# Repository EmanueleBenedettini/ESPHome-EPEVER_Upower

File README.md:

# ESPHome-EPEVER_Upower

Code and instructions for the integration of EPEVER Upower inverters in Home Assistant.

## Configuration

In `upower.yaml`, update the following values to match your setup:

- **Line 19**: `YOURAPIENCRYPTIONKEY` - Your API encryption key
- **Line 22**: `YOUROTAPASSWORD` - Your OTA password
- **Line 31**: `YOURPASSWORD` - Your device password

## Firmware Size

The code is optimized to fit on an ESP01_1M module while maintaining OTA update capability.

## Board Design

A custom PCB design is included (created with Eagle). To manufacture your board:

1. Go to a site like [jlcpcb.com](https://jlcpcb.com)
2. Upload the `Gerber.zip` file

### Components to Solder

| Designator | Value | Package |
|---|---|---|
| R5, R6 | 3.3kΩ | M1206 |
| R1, R2 | 10kΩ | M1206 |
| R4 | 120Ω | M1206 |
| U2 | AMS1117-3.3 | SOT229P700X180-4N |
| Q1 | 2N7002 N-Channel MOSFET | SOT23 |
| IC1 | MAX485 | SO08 |
| C1, C2 | 100µF | 6mm diameter |

### Notes

- **U1** (ESP01): In most cases, this does not need to be soldered. It should fit snugly in the socket.

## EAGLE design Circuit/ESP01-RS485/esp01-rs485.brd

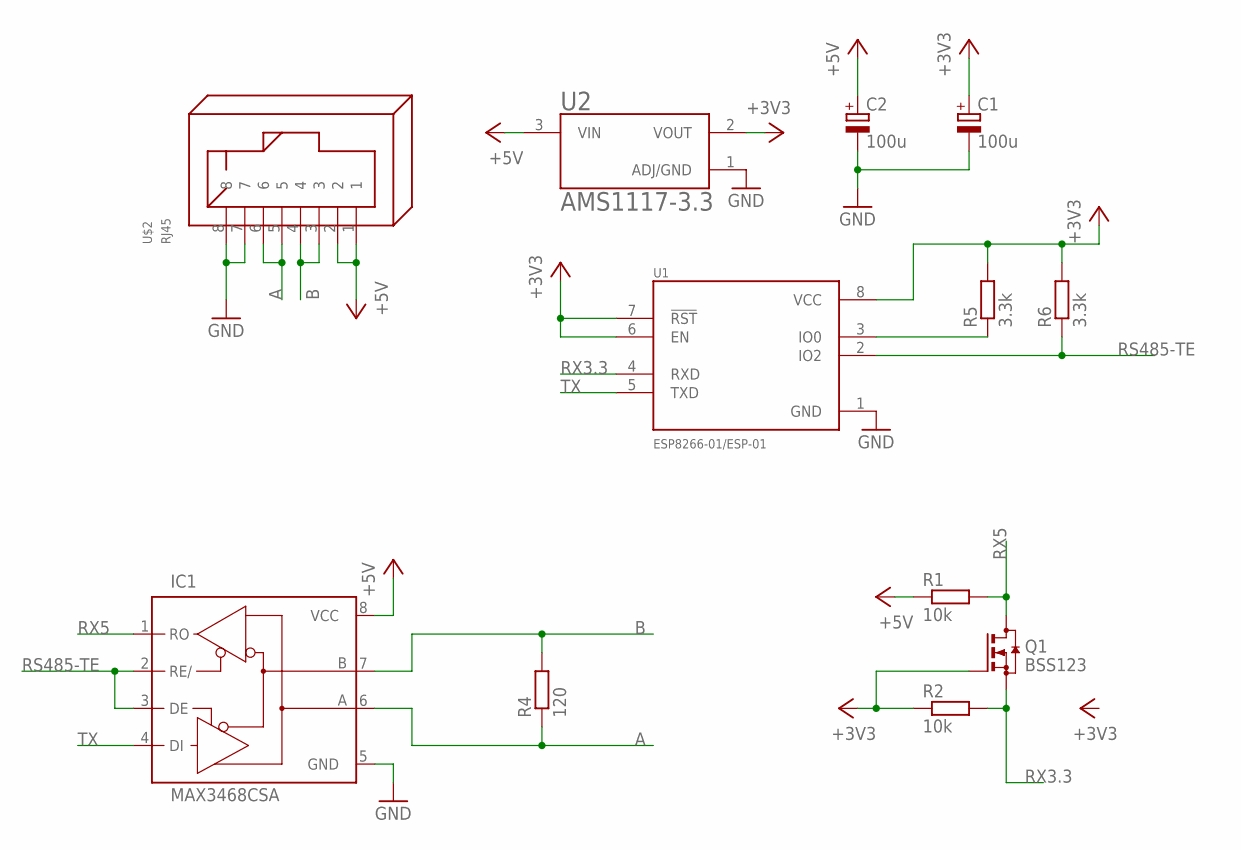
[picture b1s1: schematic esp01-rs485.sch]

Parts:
C1, C2: 100u; E2,5-6
IC1: MAX3468CSA; SO08
Q1: BSS123; SOT23
R1, R2: 10k; M1206
R4: 120; M1206
R5, R6: 3.3k; M1206
U1: ESP8266-01/ESP-01; XCVR_ESP8266-01/ESP-01
U2: AMS1117-3.3; SOT229P700X180-4N
U$2: RJ45

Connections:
+3V3: C1.+, Q1.1 (G), R2.1, R5.2, R6.2, U1.6 (EN), U1.7 (!RST), U1.8 (VCC), U2.2 (VOUT)
+5V: C2.+, IC1.8 (VCC), R1.1, U2.3 (VIN), U$2.1, U$2.2
A: IC1.6 (A), R4.1, U$2.5, U$2.6
B: IC1.7 (B), R4.2, U$2.3, U$2.4
GND: C1.-, C2.-, IC1.5 (GND), U1.1 (GND), U2.1 (ADJ/GND), U$2.7, U$2.8
unnamed: R5.1, U1.3 (IO0)
RS485-TE: IC1.2 (RE/), IC1.3 (DE), R6.1, U1.2 (IO2)
RX3.3: Q1.2 (S), R2.2, U1.4 (RXD)
RX5: IC1.1 (RO), Q1.3 (D), R1.2
TX: IC1.4 (DI), U1.5 (TXD)

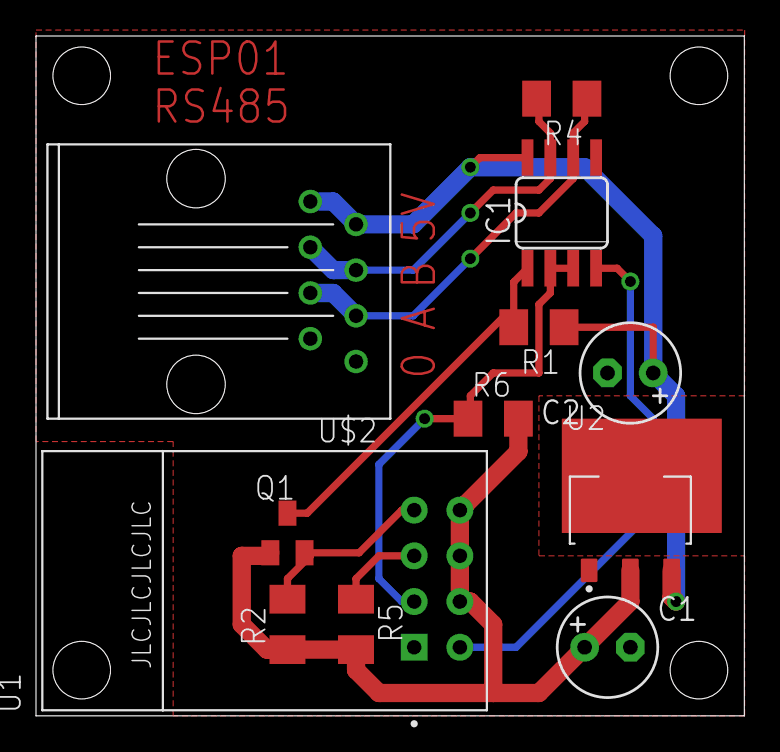
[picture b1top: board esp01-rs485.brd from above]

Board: 2 copper layers, 39.4 x 37.8 mm, 12 parts (0 on the bottom side), 10 nets.

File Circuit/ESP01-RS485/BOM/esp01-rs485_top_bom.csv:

Comment,Designator,Footprint,LCSC Part #
3.3k,R5 R6,M1206,
10k,R1 R2,M1206,
120,R4,M1206,
AMS1117-3.3,U2,SOT229P700X180-4N,
BSS123,Q1,SOT23,
MAX3468CSA,IC1,SO08,

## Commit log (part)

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2024-01-07 add files
2026-05-01 Update README.md readability
